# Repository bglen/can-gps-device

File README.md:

# can-gps-device

| Side      | Top |
| ----------- | ----------- |
|       |        |

Simple, easy to use GPS module for CAN bus-networked vehicles.
- ublox NEO-M90V-20B GNSS + IMU dead reckoning module
- STM32F042
- CAN 2.0B
- Super capacitor circuit supports hot-start up to 30 minutes after first lock
- ublox ANN-MB5 antenna recomended

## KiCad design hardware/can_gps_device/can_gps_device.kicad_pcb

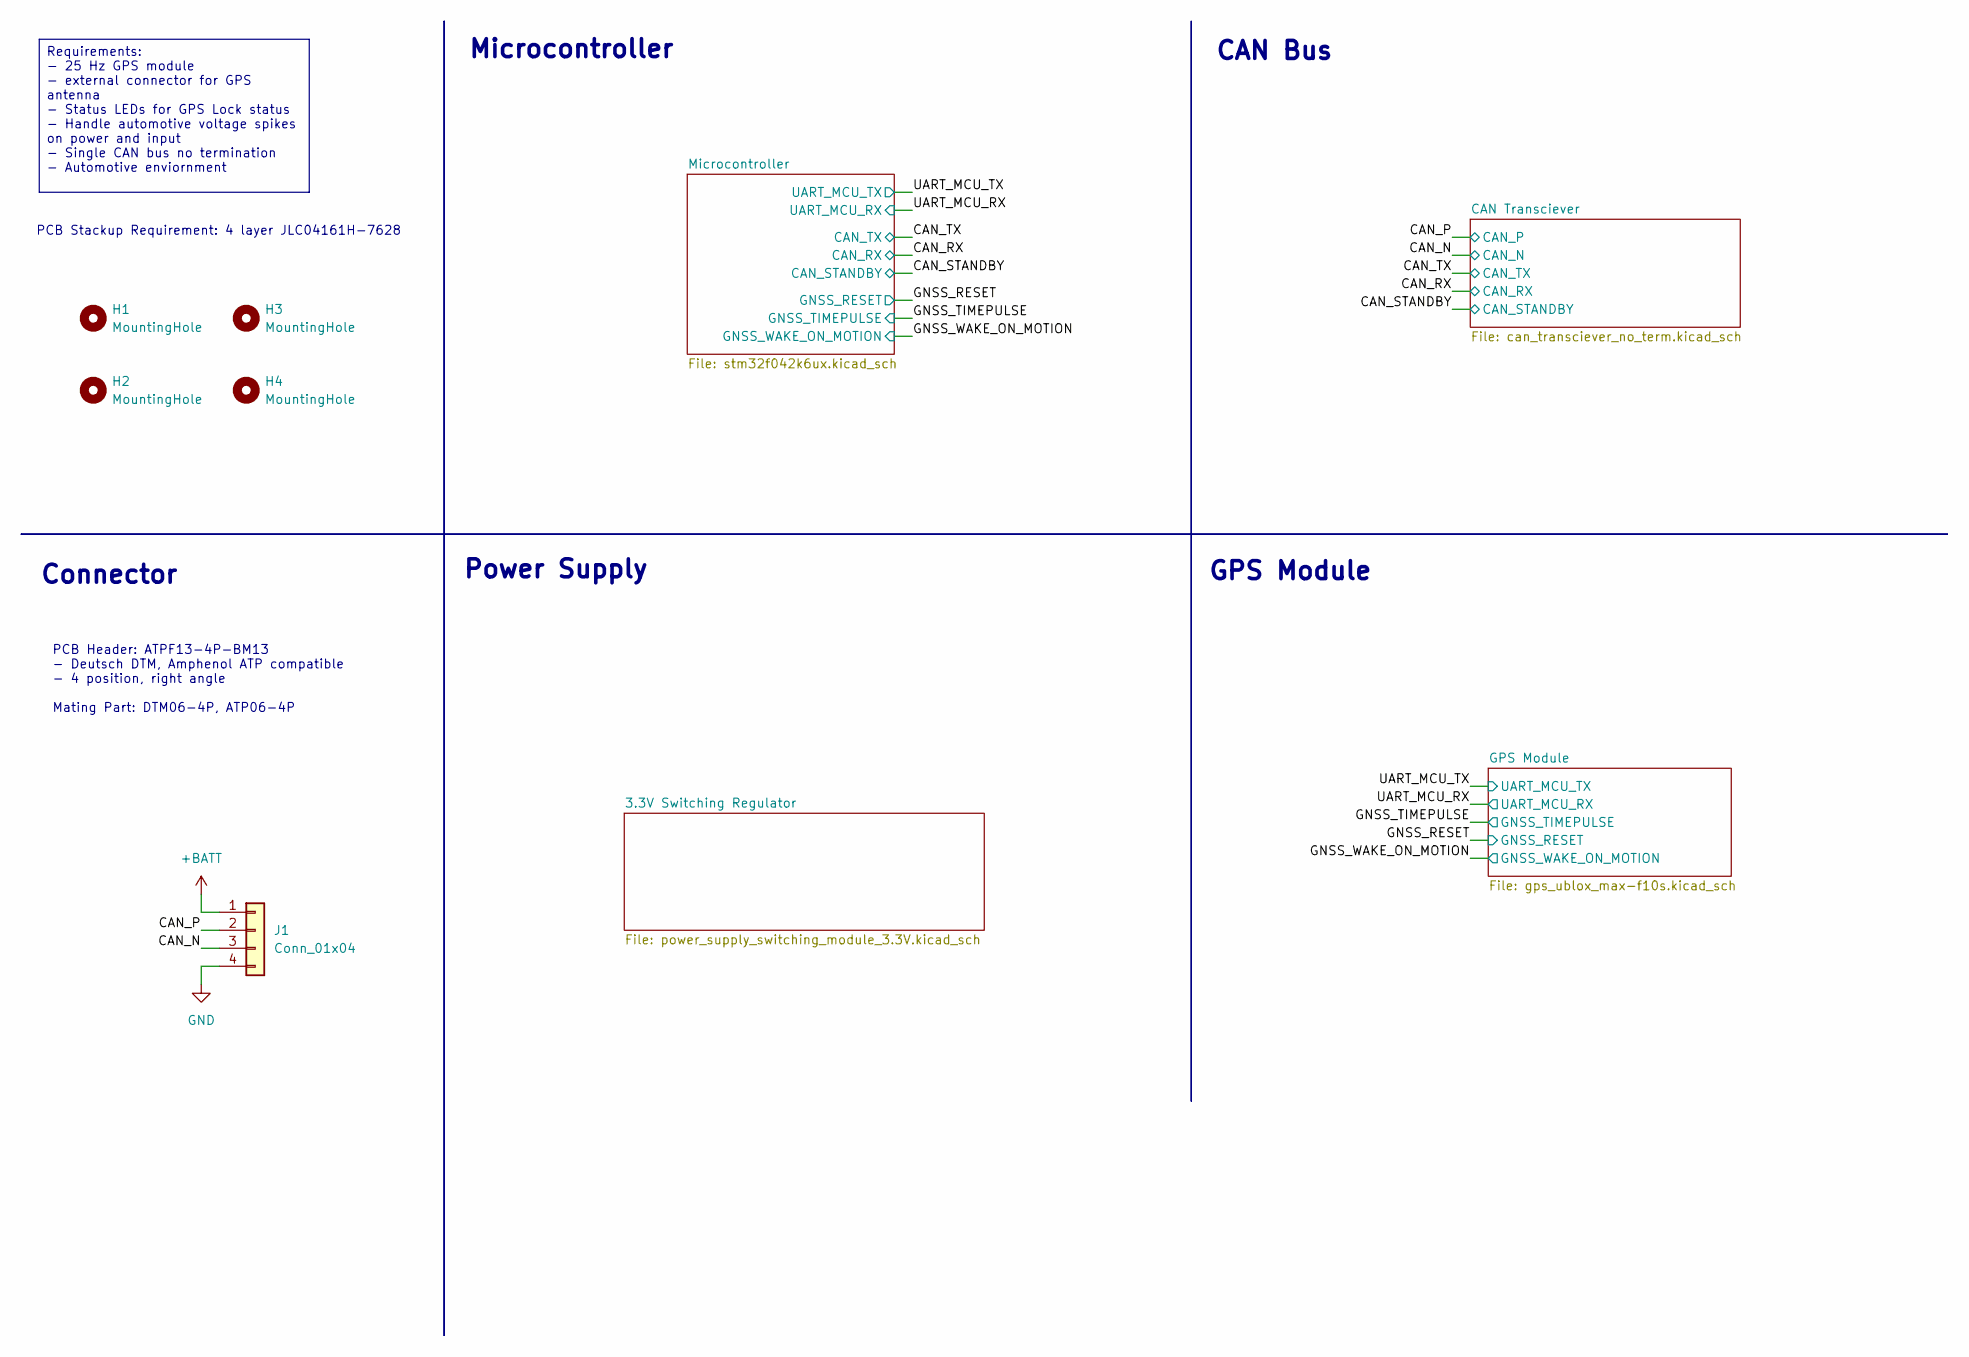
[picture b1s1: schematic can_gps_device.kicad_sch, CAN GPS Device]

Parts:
H1, H2, H3, H4: MountingHole; MountingHole_3.2mm_M3
J1: Conn_01x04; ATF13-4P-BM13_AMP

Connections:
+BATT: J1.1; also elsewhere on the board
/CAN_N: J1.3; also elsewhere on the board
/CAN_P: J1.2; also elsewhere on the board
GND: J1.4; also elsewhere on the board

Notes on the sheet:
Connector
GPS Module
PCB Header: ATPF13-4P-BM13 - Deutsch DTM, Amphenol ATP compatible - 4 position, right angle Mating Part: DTM06-4P, ATP06-4P
Power Supply
CAN Bus
PCB Stackup Requirement: 4 layer JLC04161H-7628
Microcontroller
Requirements: - 25 Hz GPS module - external connector for GPS antenna - Status LEDs for GPS Lock status - Handle automotive voltage spikes on power and input - Single CAN bus no termination - Automotive enviornment

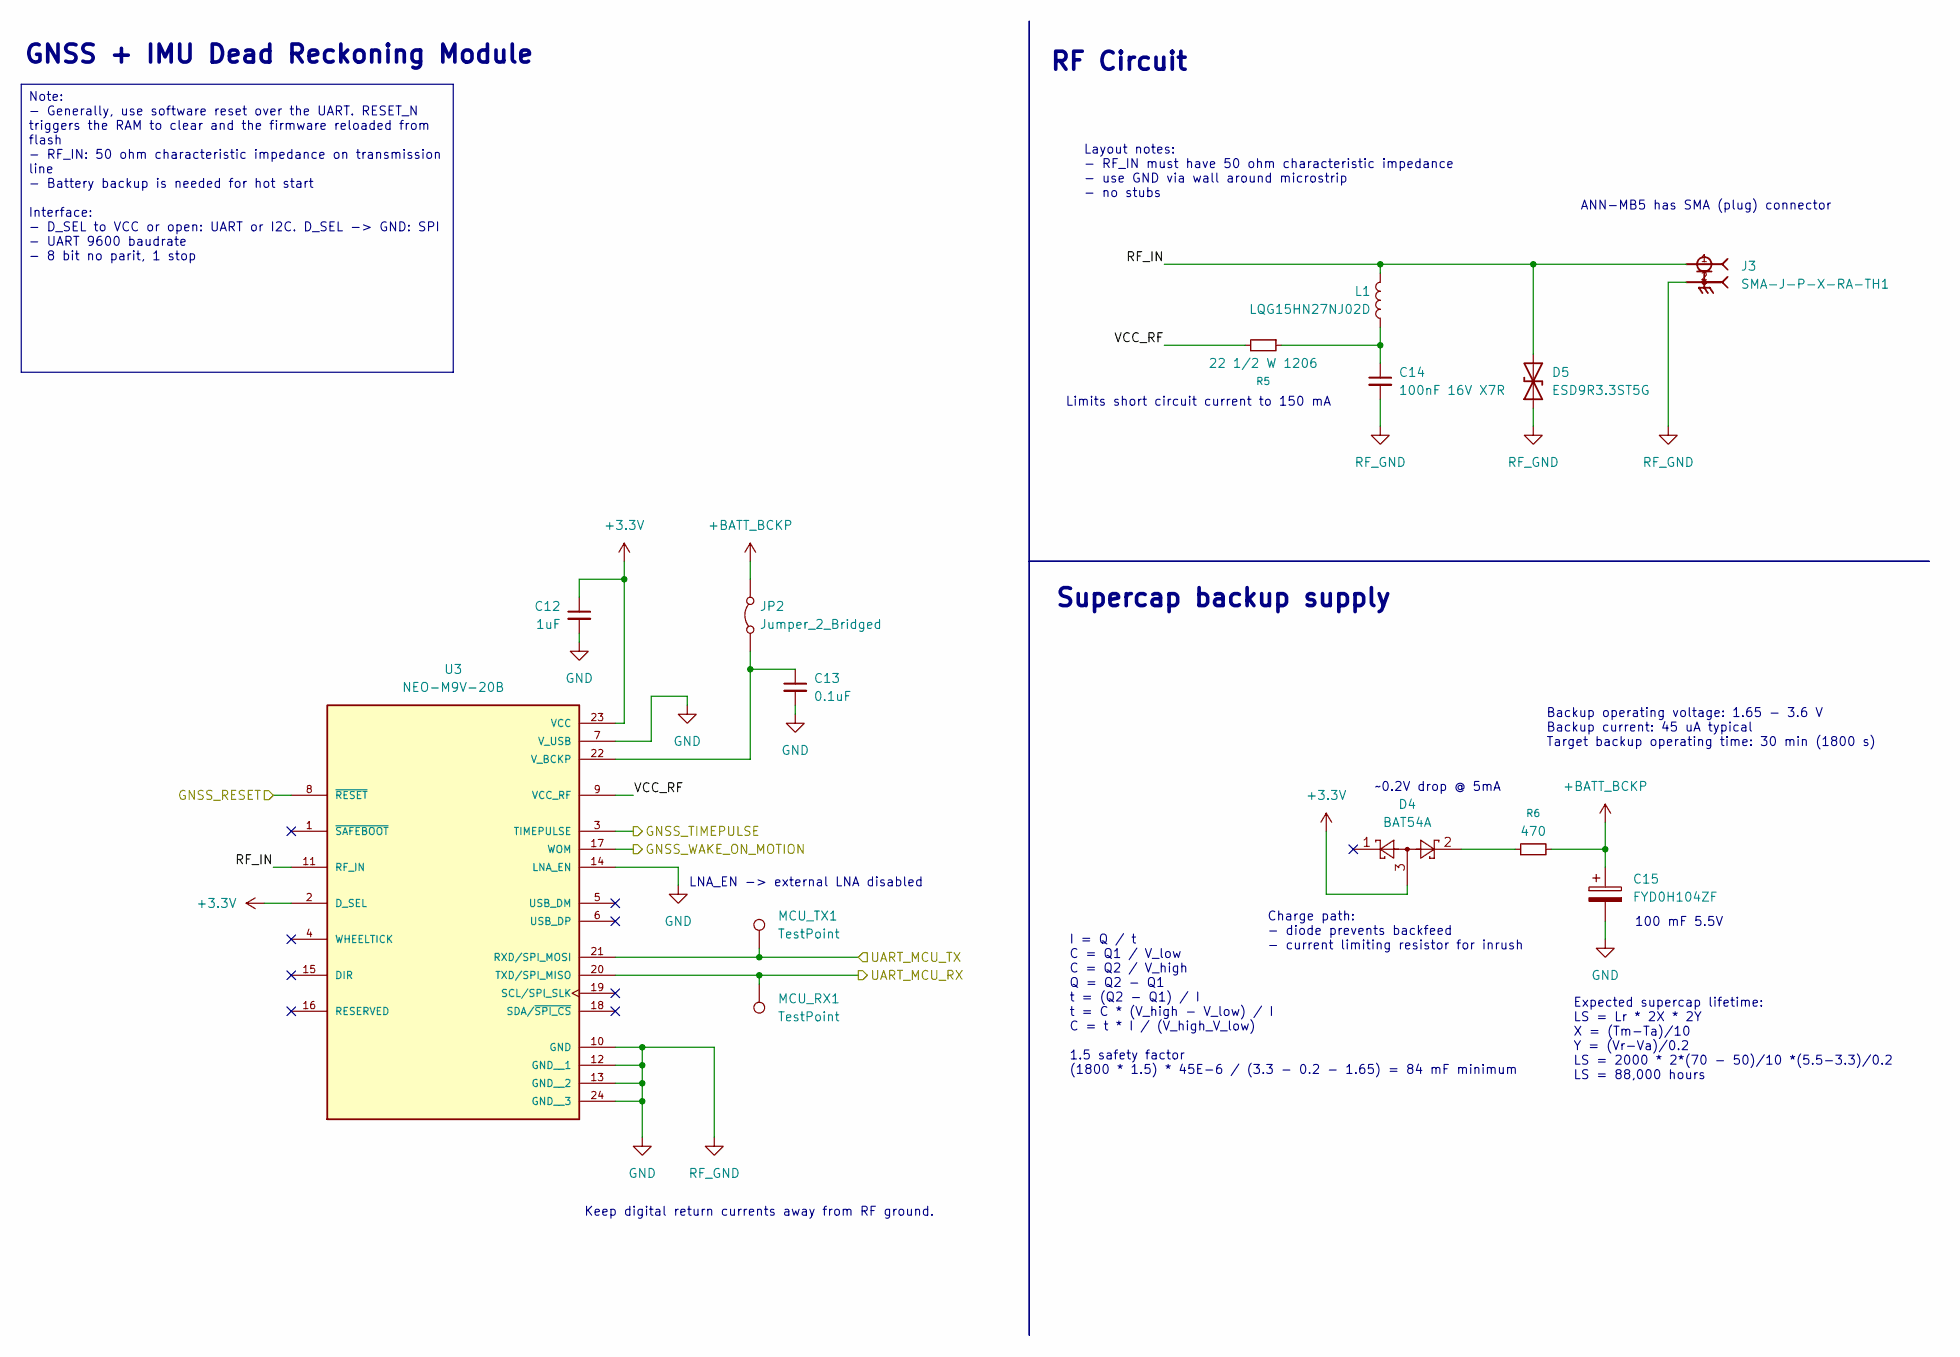
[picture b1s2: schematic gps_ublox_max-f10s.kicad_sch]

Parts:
C12: 1uF; C_0603_1608Metric
C13: 0.1uF; C_0603_1608Metric
C14: 100nF 16V X7R; C_0603_1608Metric
C15: FYD0H104ZF; CP_Radial_D13.0mm_P5.00mm
D4: BAT54A; SOT-23
D5: ESD9R3.3ST5G; D_SOD-923
J3: SMA-J-P-X-RA-TH1; SAMTEC_SMA-J-P-X-RA-TH1; PARTREV K
JP2: Jumper_2_Bridged; SolderJumper-2_P1.3mm_Bridged_RoundedPad1.0x1.5mm
L1: LQG15HN27NJ02D; L_0402_1005Metric_Pad0.77x0.64mm_HandSolder
MCU_RX1: TestPoint; TestPoint_Pad_D1.5mm
MCU_TX1: TestPoint; TestPoint_Pad_D1.5mm
R5: 22 1/2 W 1206; R_1206_3216Metric
R6: 470; R_0603_1608Metric
U3: NEO-M9V-20B; XCVR_NEO-M9V-20B; PARTREV C1

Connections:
+3.3V: C12.1, D4.3, U3.2 (D_SEL), U3.23 (VCC); also elsewhere on the board
+BATT_BCKP: C15.1, JP2.2 (B), R6.2
/GNSS_RESET: U3.8 (~RESET); also elsewhere on the board
/GNSS_TIMEPULSE: U3.3 (TIMEPULSE); also elsewhere on the board
/GNSS_WAKE_ON_MOTION: U3.17 (WOM); also elsewhere on the board
/GPS Module/RF_IN: D5.2 (A2), J3.1, L1.1, U3.11 (RF_IN)
/GPS Module/VCC_RF: R5.2, U3.9 (VCC_RF)
/UART_MCU_RX: MCU_RX1.1, U3.20 (TXD/SPI_MISO); also elsewhere on the board
/UART_MCU_TX: MCU_TX1.1, U3.21 (RXD/SPI_MOSI); also elsewhere on the board
GND: C12.2, C13.2, C14.2, C15.2, D5.1 (A1), J3.2, J3.3, J3.4, J3.5, U3.7 (V_USB), U3.10 (GND), U3.12 (GND__1), U3.13 (GND__2), U3.14 (LNA_EN), U3.24 (GND__3); also elsewhere on the board
unnamed: C14.1, L1.2, R5.1
unnamed: D4.2, R6.1
unnamed: C13.1, JP2.1 (A), U3.22 (V_BCKP)

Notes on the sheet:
Layout notes: - RF_IN must have 50 ohm characteristic impedance - use GND via wall around microstrip - no stubs
RF Circuit
Backup operating voltage: 1.65 - 3.6 V Backup current: 45 uA typical Target backup operating time: 30 min (1800 s)
Limits short circuit current to 150 mA
~0.2V drop @ 5mA
100 mF 5.5V
ANN-MB5 has SMA (plug) connector
LNA_EN -> external LNA disabled
I = Q / t C = Q1 / V_low C = Q2 / V_high Q = Q2 - Q1 t = (Q2 - Q1) / I t = C * (V_high - V_low) / I C = t * I / (V_high_V_low) 1.5 safety factor (1800 * 1.5) * 45E-6 / (3.3 - 0.2 - 1.65) = 84 mF minimum
Expected supercap lifetime: LS = Lr * 2X * 2Y X = (Tm-Ta)/10 Y = (Vr-Va)/0.2 LS = 2000 * 2*(70 - 50)/10 *(5.5-3.3)/0.2 LS = 88,000 hours
GNSS + IMU Dead Reckoning Module
Keep digital return currents away from RF ground.
Supercap backup supply
Charge path: - diode prevents backfeed - current limiting resistor for inrush
Note: - Generally, use software reset over the UART. RESET_N triggers the RAM to clear and the firmware reloaded from flash - RF_IN: 50 ohm characteristic impedance on transmission line - Battery backup is needed for hot start Interface: - D_SEL to VCC or open: UART or I2C. D_SEL -> GND: SPI - UART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

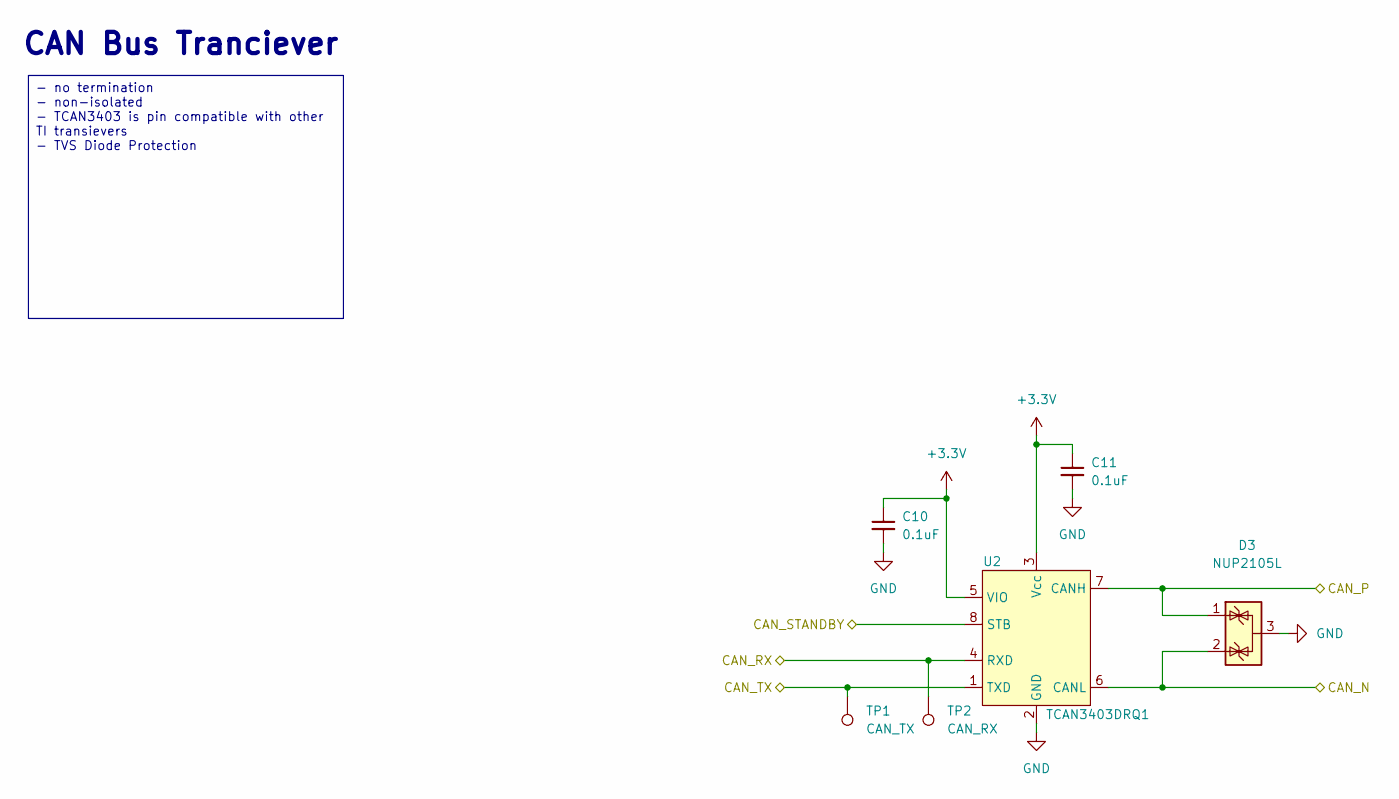
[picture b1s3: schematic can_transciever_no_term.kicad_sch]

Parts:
C10, C11: 0.1uF; C_0603_1608Metric
D3: NUP2105L; SOT-23
TP1: CAN_TX; TestPoint_Pad_D1.5mm
TP2: CAN_RX; TestPoint_Pad_D1.5mm
U2: TCAN3403DRQ1; SOIC-8_3.9x4.9mm_P1.27mm

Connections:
+3.3V: C10.1, C11.1, U2.3 (Vcc), U2.5 (VIO); also elsewhere on the board
/CAN_N: D3.2 (K), U2.6 (CANL); also elsewhere on the board
/CAN_P: D3.1 (K), U2.7 (CANH); also elsewhere on the board
/CAN_RX: TP2.1, U2.4 (RXD); also elsewhere on the board
/CAN_STANDBY: U2.8 (STB); also elsewhere on the board
/CAN_TX: TP1.1, U2.1 (TXD); also elsewhere on the board
GND: C10.2, C11.2, D3.3 (A), U2.2 (GND); also elsewhere on the board

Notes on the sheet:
CAN Bus Tranciever
- no termination - non-isolated - TCAN3403 is pin compatible with other TI transievers - TVS Diode Protection

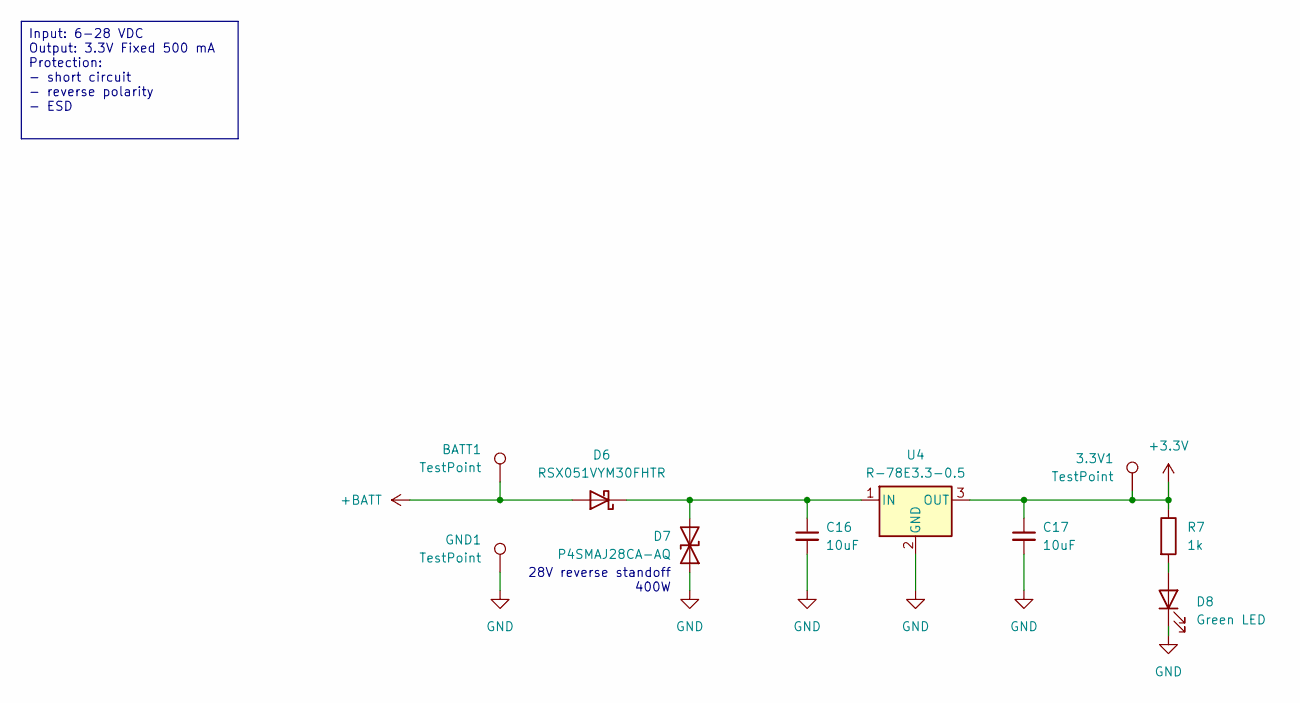
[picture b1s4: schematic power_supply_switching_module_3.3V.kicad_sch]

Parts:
3.3V1: TestPoint; TestPoint_Pad_D1.5mm
BATT1: TestPoint; TestPoint_Pad_D1.5mm
C16, C17: 10uF; C_0805_2012Metric
D6: RSX051VYM30FHTR; D_TUMD2
D7: P4SMAJ28CA-AQ; D_SMA
D8: Green LED; LED_0603_1608Metric
GND1: TestPoint; TestPoint_Pad_D1.5mm
R7: 1k; R_0603_1608Metric
U4: R-78E3.3-0.5; Converter_DCDC_RECOM_R-78E-0.5_THT

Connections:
+3.3V: 3.3V1.1, C17.1, R7.1, U4.3 (OUT); also elsewhere on the board
+BATT: BATT1.1, D6.2 (A); also elsewhere on the board
GND: C16.2, C17.2, D7.1 (A1), D8.1 (K), GND1.1, U4.2 (GND); also elsewhere on the board
unnamed: C16.1, D6.1 (K), D7.2 (A2), U4.1 (IN)
unnamed: D8.2 (A), R7.2

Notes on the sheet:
28V reverse standoff 400W
Input: 6-28 VDC Output: 3.3V Fixed 500 mA Protection: - short circuit - reverse polarity - ESD

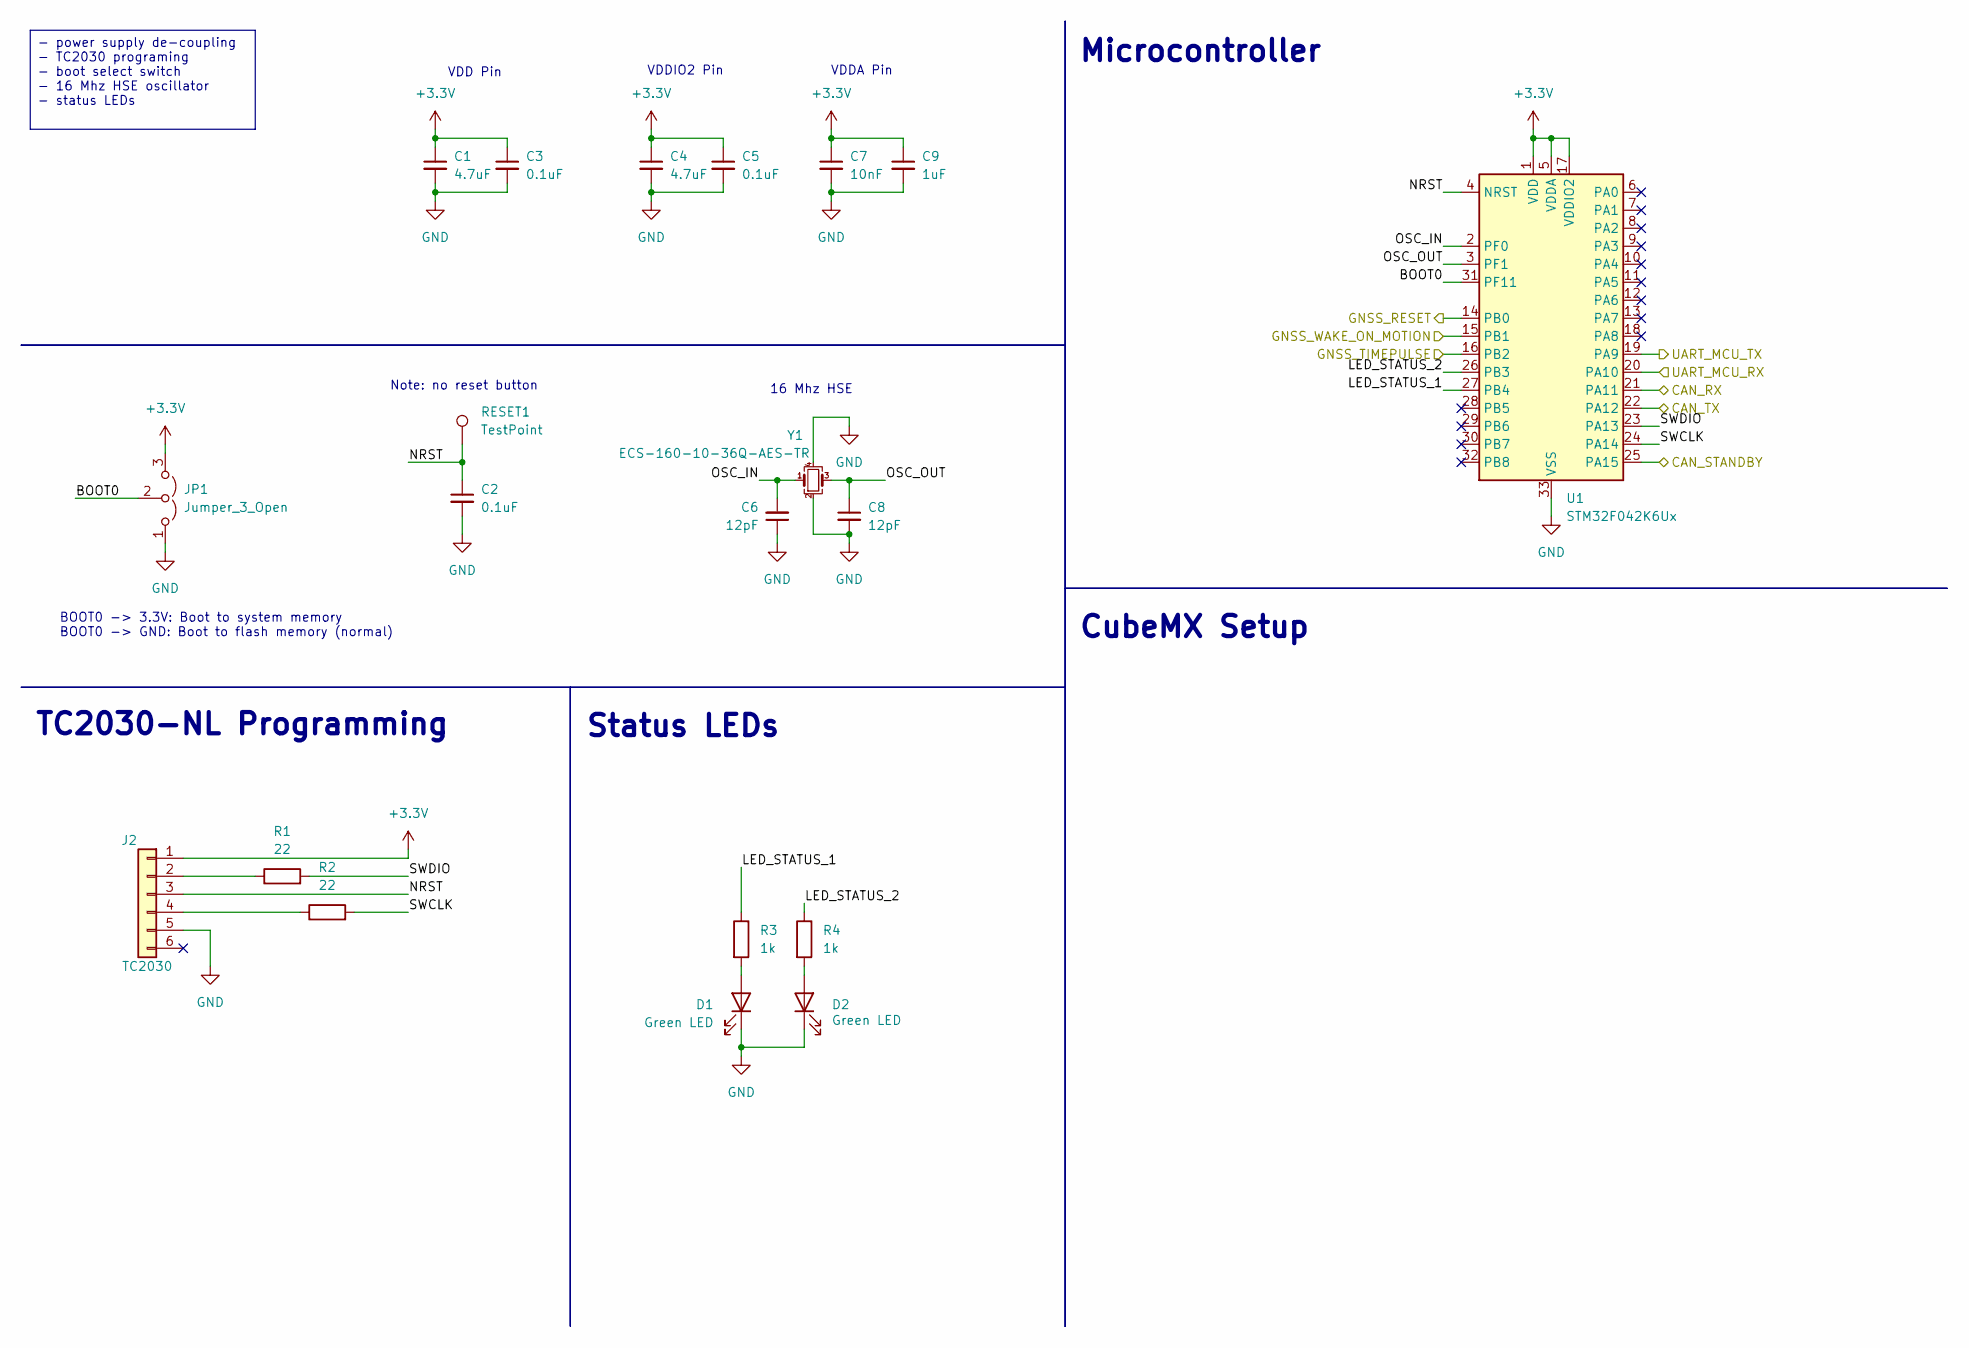
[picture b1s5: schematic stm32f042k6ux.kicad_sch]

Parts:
C1, C4: 4.7uF; C_0603_1608Metric
C2, C3, C5: 0.1uF; C_0603_1608Metric
C6, C8: 12pF; C_0603_1608Metric
C7: 10nF; C_0603_1608Metric
C9: 1uF; C_0603_1608Metric
D1, D2: Green LED; LED_0603_1608Metric
J2: TC2030; Tag-Connect_TC2030-IDC-NL_2x03_P1.27mm_Vertical
JP1: Jumper_3_Open; SolderJumper-3_P1.3mm_Open_RoundedPad1.0x1.5mm
R1, R2: 22; R_0603_1608Metric
R3, R4: 1k; R_0603_1608Metric
RESET1: TestPoint; TestPoint_Pad_D1.5mm
U1: STM32F042K6Ux; QFN-32-1EP_5x5mm_P0.5mm_EP3.45x3.45mm
Y1: ECS-160-10-36Q-AES-TR; Crystal_SMD_2520-4Pin_2.5x2.0mm

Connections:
+3.3V: C1.1, C3.1, C4.1, C5.1, C7.1, C9.1, J2.1, JP1.3 (B), U1.1 (VDD), U1.5 (VDDA), U1.17 (VDDIO2); also elsewhere on the board
/CAN_RX: U1.21 (PA11); also elsewhere on the board
/CAN_STANDBY: U1.25 (PA15); also elsewhere on the board
/CAN_TX: U1.22 (PA12); also elsewhere on the board
/GNSS_RESET: U1.14 (PB0); also elsewhere on the board
/GNSS_TIMEPULSE: U1.16 (PB2); also elsewhere on the board
/GNSS_WAKE_ON_MOTION: U1.15 (PB1); also elsewhere on the board
/Microcontroller/BOOT0: JP1.2 (C), U1.31 (PF11)
/Microcontroller/LED_STATUS_1: R3.1, U1.27 (PB4)
/Microcontroller/LED_STATUS_2: R4.1, U1.26 (PB3)
/Microcontroller/NRST: C2.1, J2.3, RESET1.1, U1.4 (NRST)
/Microcontroller/OSC_IN: C6.2, U1.2 (PF0), Y1.1
/Microcontroller/OSC_OUT: C8.1, U1.3 (PF1), Y1.3
/Microcontroller/SWCLK: R2.2, U1.24 (PA14)
/Microcontroller/SWDIO: R1.2, U1.23 (PA13)
/UART_MCU_RX: U1.20 (PA10); also elsewhere on the board
/UART_MCU_TX: U1.19 (PA9); also elsewhere on the board
GND: C1.2, C2.2, C3.2, C4.2, C5.2, C6.1, C7.2, C8.2, C9.2, D1.1 (K), D2.1 (K), J2.5, JP1.1 (A), U1.33 (VSS), Y1.2, Y1.4; also elsewhere on the board
unnamed: D1.2 (A), R3.2
unnamed: D2.2 (A), R4.2
unnamed: J2.2, R1.1
unnamed: J2.4, R2.1

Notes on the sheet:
Microcontroller
VDD Pin
TC2030-NL Programming
Note: no reset button
16 Mhz HSE
CubeMX Setup
VDDA Pin
BOOT0 -> 3.3V: Boot to system memory BOOT0 -> GND: Boot to flash memory (normal)
Status LEDs
VDDIO2 Pin
- power supply de-coupling - TC2030 programing - boot select switch - 16 Mhz HSE oscillator - status LEDs

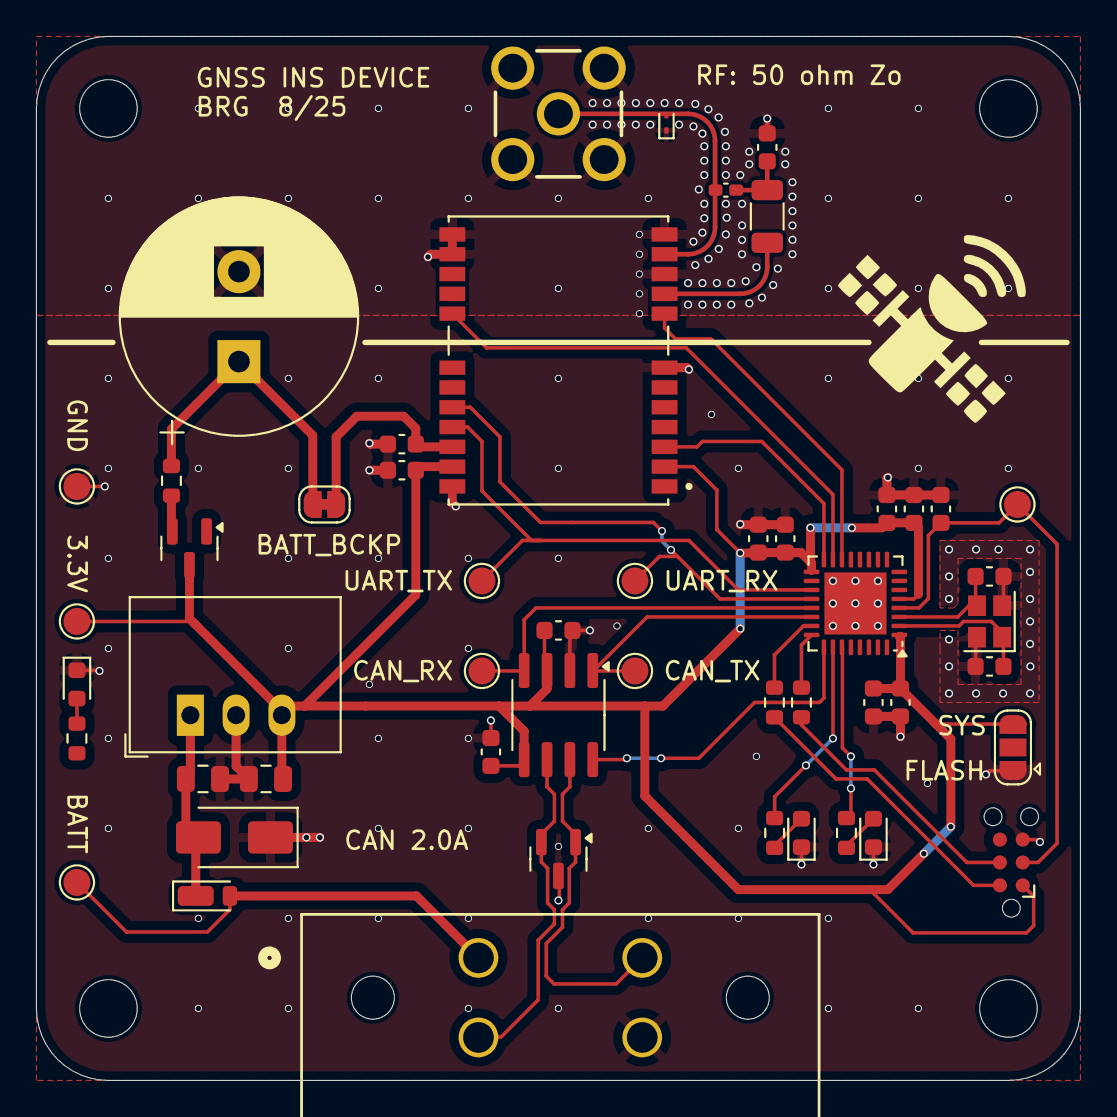
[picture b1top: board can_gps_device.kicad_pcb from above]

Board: 4 copper layers, 58.0 x 58.0 mm, 55 parts (0 on the bottom side), 33 nets.

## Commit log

2025-08-21 Schematic Initial Rev
2025-08-21 PCB design rev 1
2025-08-21 Updated MX config and schematic PDF
